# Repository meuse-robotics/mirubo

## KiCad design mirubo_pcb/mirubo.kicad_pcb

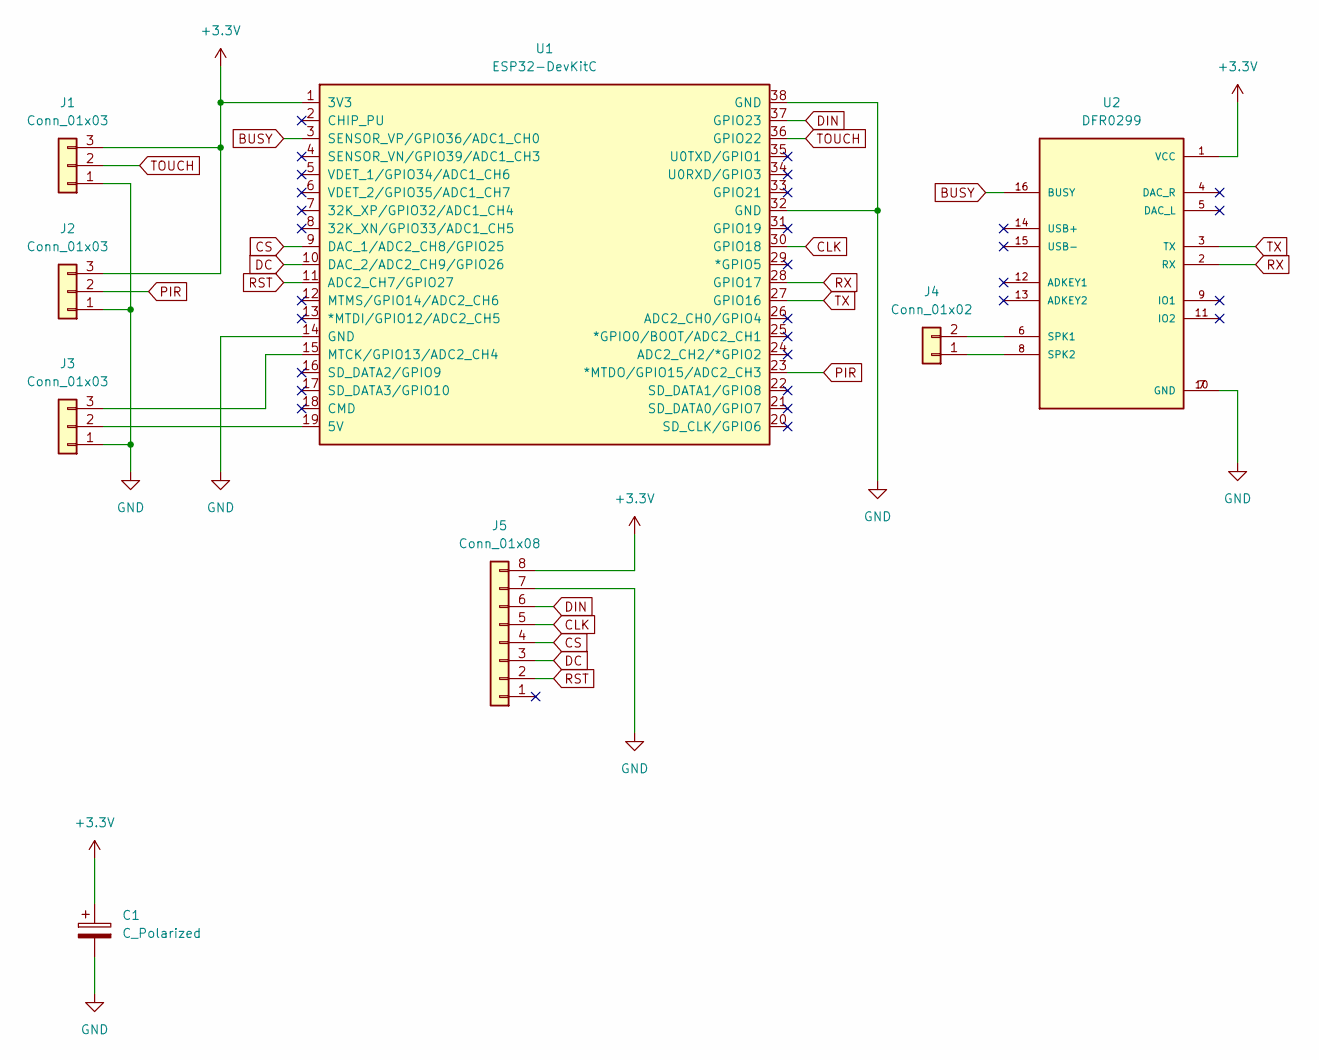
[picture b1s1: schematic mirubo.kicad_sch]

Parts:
C1: C_Polarized; CP_Radial_D5.0mm_P2.50mm
J1, J2, J3: Conn_01x03; PinHeader_1x03_P2.54mm_Vertical
J4: Conn_01x02; PinHeader_1x02_P2.54mm_Vertical
J5: Conn_01x08; PinHeader_1x08_P2.54mm_Vertical
U1: ESP32-DevKitC
U2: DFR0299; MODULE_DFR0299

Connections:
+3.3V: C1.1, J1.3, J2.3, J5.8, U1.1 (3V3), U2.1 (VCC)
BUSY: U1.3 (SENSOR_VP/GPIO36/ADC1_CH0), U2.16 (BUSY)
CLK: J5.5, U1.30 (GPIO18)
CS: J5.4, U1.9 (DAC_1/ADC2_CH8/GPIO25)
DC: J5.3, U1.10 (DAC_2/ADC2_CH9/GPIO26)
DIN: J5.6, U1.37 (GPIO23)
GND: C1.2, J1.1, J2.1, J3.1, J5.7, U1.14 (GND), U1.32 (GND), U1.38 (GND), U2.7 (GND), U2.10 (GND)
unnamed: J3.2, U1.19 (5V)
unnamed: J3.3, U1.15 (MTCK/GPIO13/ADC2_CH4)
unnamed: J4.1, U2.8 (SPK2)
unnamed: J4.2, U2.6 (SPK1)
PIR: J2.2, U1.23 (*MTDO/GPIO15/ADC2_CH3)
RST: J5.2, U1.11 (ADC2_CH7/GPIO27)
RX: U1.28 (GPIO17), U2.2 (RX)
TOUCH: J1.2, U1.36 (GPIO22)
TX: U1.27 (GPIO16), U2.3 (TX)

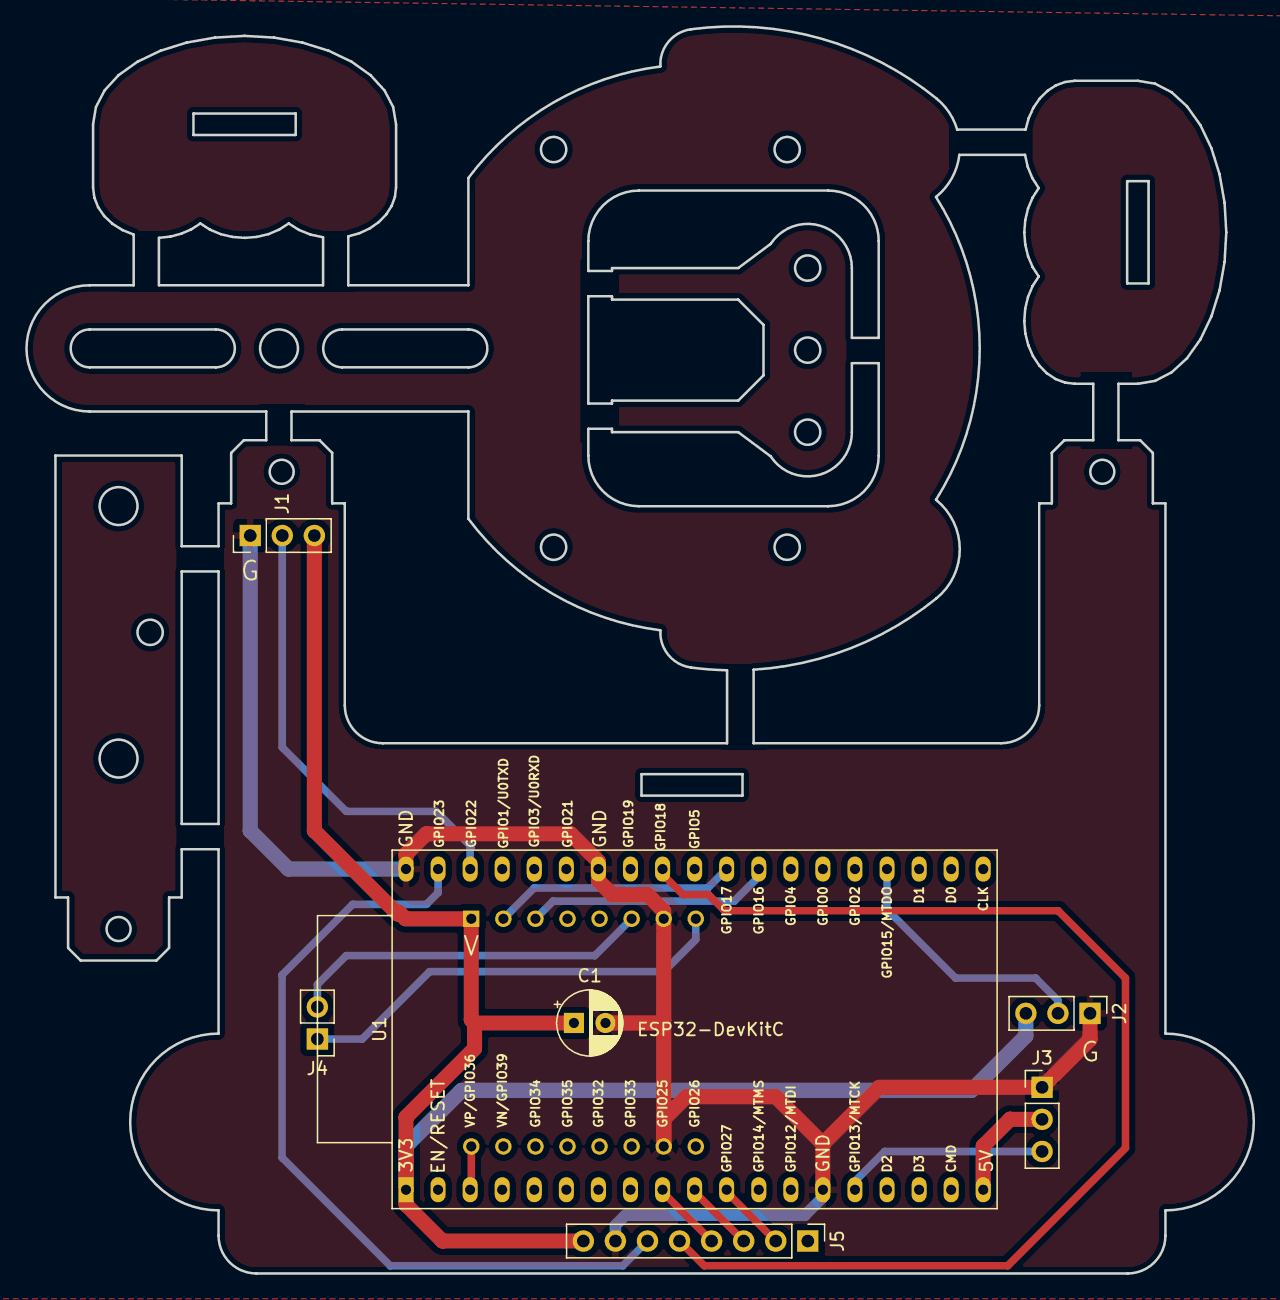
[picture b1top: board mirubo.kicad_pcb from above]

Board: 2 copper layers, 97.2 x 98.8 mm, 8 parts (1 on the bottom side), 16 nets.
